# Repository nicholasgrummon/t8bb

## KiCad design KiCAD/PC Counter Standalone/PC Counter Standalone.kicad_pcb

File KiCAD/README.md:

# KiCAD Schematics
I originally designed and assembled t8bb in January 2022 as a hobby project in college (just in my free time, not for credit).<br>
I revisited the project in Fall 2024 after graduating to consider upgrading the computer into a more robust PCB kit that I could potentially sell.
Here I have committed my KiCAD schematics and PCB layouts for the intended upgrade.<br>
However, the upgrade did not come to pass at the time because the supplier I ended up ordering from applied the SMD LEDs backwards.<br>
Not realizing this, I burned out the LEDs on the first board I powered up. I had ordered a handful and tried to desolder and reorient the other LEDs but ruined the boards.
I tried to place several more smaller orders with the same supplier, but they reversed the polarity of the LEDs each time.
So I had to give up on making PCBs for the time.<br>

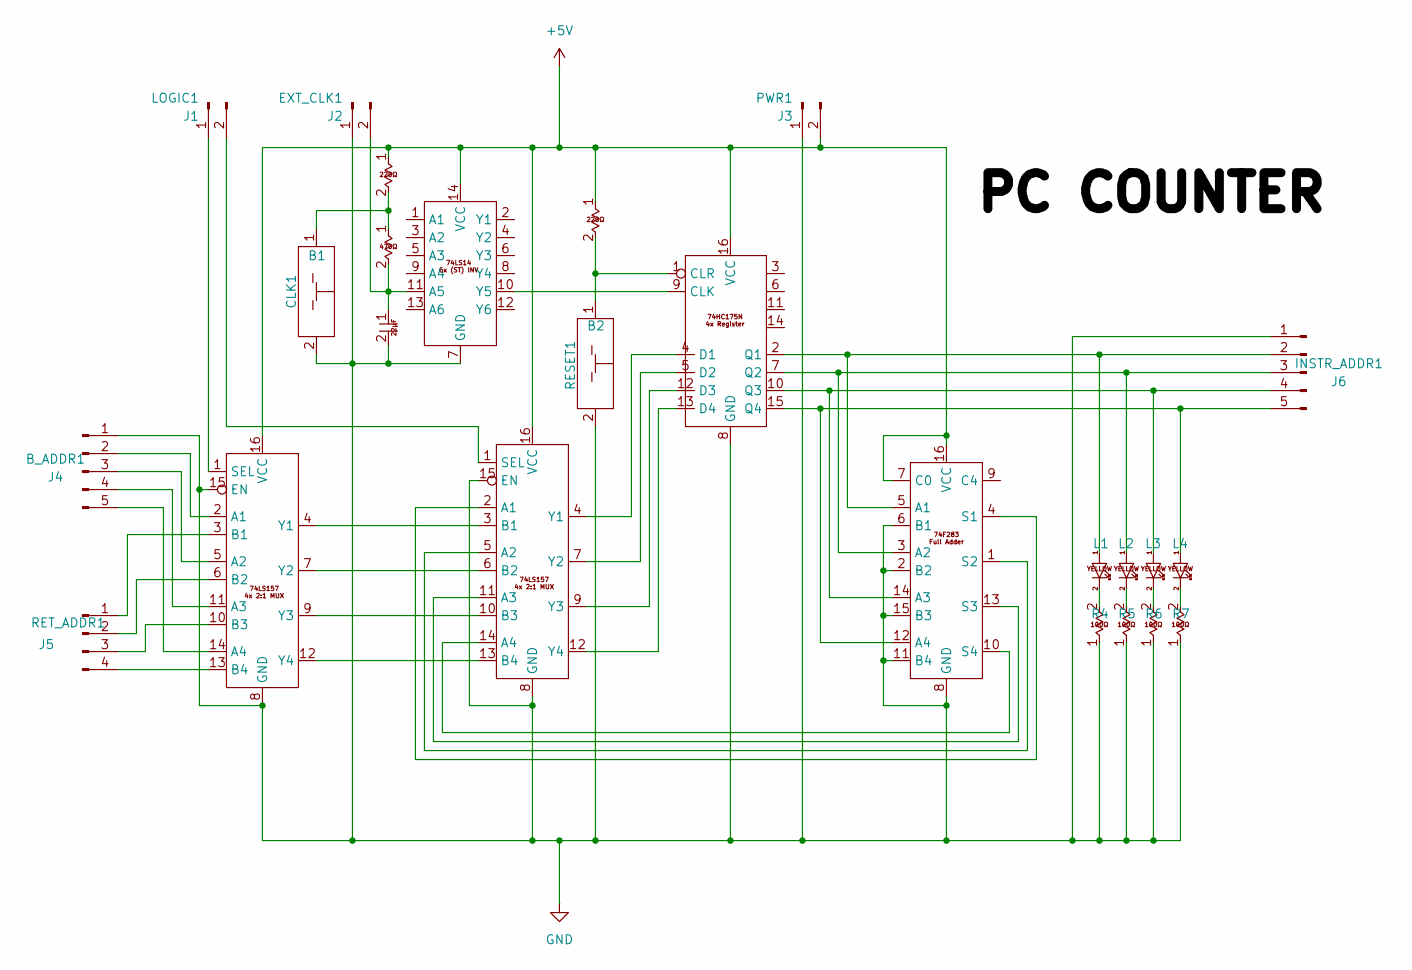
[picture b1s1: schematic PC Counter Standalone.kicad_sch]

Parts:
22μF1: C1; CP_Elec_4x5.4
100Ω1: R4; R_0805_2012Metric
100Ω2: R5; R_0805_2012Metric
100Ω3: R6; R_0805_2012Metric
100Ω4: R7; R_0805_2012Metric
220Ω1: R1; R_0805_2012Metric
220Ω2: R3; R_0805_2012Metric
470Ω1: R2; R_0805_2012Metric
ADD1: U5; 16pinbase
B_ADDR1: J4; PinHeader_1x05_P2.54mm_Vertical
CLK1: B1; SW_Tactile_SPST_NO_Straight_CK_PTS636Sx25SMTRLFS; LCSC C7419906
EXT_CLK1: J2; PinHeader_1x02_P2.54mm_Vertical
INSTR_ADDR1: J6; PinHeader_1x05_P2.54mm_Vertical
LED_YELLOW1: L1; LED_0805_2012Metric; LCSC C2296
LED_YELLOW2: L2; LED_0805_2012Metric; LCSC C2296
LED_YELLOW3: L3; LED_0805_2012Metric; LCSC C2296
LED_YELLOW4: L4; LED_0805_2012Metric; LCSC C2296
LOGIC1: J1; PinHeader_1x02_P2.54mm_Vertical
MUX1: U3; 16pinbase; LCSC C707097
MUX2: U4; 16pinbase
PWR1: J3; PinHeader_1x02_P2.54mm_Vertical
REG1: U2; 16pinbase
RESET1: B2; SW_Tactile_SPST_NO_Straight_CK_PTS636Sx25SMTRLFS; LCSC C7419906
RET_ADDR1: J5; PinHeader_1x04_P2.54mm_Vertical
ST_INV1: U1; 14pinbase; LCSC C609749

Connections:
+5V: 220Ω1.1, 220Ω2.1, ADD1.7 (C0), ADD1.16 (VCC), MUX1.16 (VCC), MUX2.16 (VCC), PWR1.2, REG1.16 (VCC), ST_INV1.14 (VCC)
GND: 22μF1.2, 100Ω1.1, 100Ω2.1, 100Ω3.1, 100Ω4.1, ADD1.2 (B2), ADD1.6 (B1), ADD1.8 (GND), ADD1.11 (B4), ADD1.15 (B3), B_ADDR1.1, CLK1.2, EXT_CLK1.1, INSTR_ADDR1.1, MUX1.8 (GND), MUX1.15 (EN), MUX2.8 (GND), MUX2.15 (EN), PWR1.1, REG1.8 (GND), RESET1.2, ST_INV1.7 (GND)
unnamed: 100Ω1.2, LED_YELLOW1.2
unnamed: 100Ω2.2, LED_YELLOW2.2
unnamed: 100Ω3.2, LED_YELLOW3.2
unnamed: 100Ω4.2, LED_YELLOW4.2
unnamed: 220Ω1.2, 470Ω1.1, CLK1.1
unnamed: ADD1.5 (A1), INSTR_ADDR1.2, LED_YELLOW1.1, REG1.2 (Q1)
unnamed: ADD1.3 (A2), INSTR_ADDR1.3, LED_YELLOW2.1, REG1.7 (Q2)
unnamed: ADD1.14 (A3), INSTR_ADDR1.4, LED_YELLOW3.1, REG1.10 (Q3)
unnamed: ADD1.12 (A4), INSTR_ADDR1.5, LED_YELLOW4.1, REG1.15 (Q4)
unnamed: ADD1.4 (S1), MUX2.2 (A1)
unnamed: ADD1.1 (S2), MUX2.5 (A2)
unnamed: ADD1.13 (S3), MUX2.11 (A3)
unnamed: ADD1.10 (S4), MUX2.14 (A4)
unnamed: B_ADDR1.2, MUX1.2 (A1)
unnamed: B_ADDR1.3, MUX1.5 (A2)
unnamed: B_ADDR1.4, MUX1.11 (A3)
unnamed: B_ADDR1.5, MUX1.14 (A4)
unnamed: 22μF1.1, 470Ω1.2, EXT_CLK1.2, ST_INV1.11 (A5)
unnamed: LOGIC1.1, MUX1.1 (SEL)
unnamed: LOGIC1.2, MUX2.1 (SEL)
unnamed: MUX1.3 (B1), RET_ADDR1.1
unnamed: MUX1.6 (B2), RET_ADDR1.2
unnamed: MUX1.10 (B3), RET_ADDR1.3
unnamed: MUX1.13 (B4), RET_ADDR1.4
unnamed: MUX1.4 (Y1), MUX2.3 (B1)
unnamed: MUX1.7 (Y2), MUX2.6 (B2)
unnamed: MUX1.9 (Y3), MUX2.10 (B3)
unnamed: MUX1.12 (Y4), MUX2.13 (B4)
unnamed: MUX2.4 (Y1), REG1.4 (D1)
unnamed: MUX2.7 (Y2), REG1.5 (D2)
unnamed: MUX2.9 (Y3), REG1.12 (D3)
unnamed: MUX2.12 (Y4), REG1.13 (D4)
unnamed: REG1.9 (CLK), ST_INV1.10 (Y5)
unnamed: 220Ω2.2, REG1.1 (CLR), RESET1.1

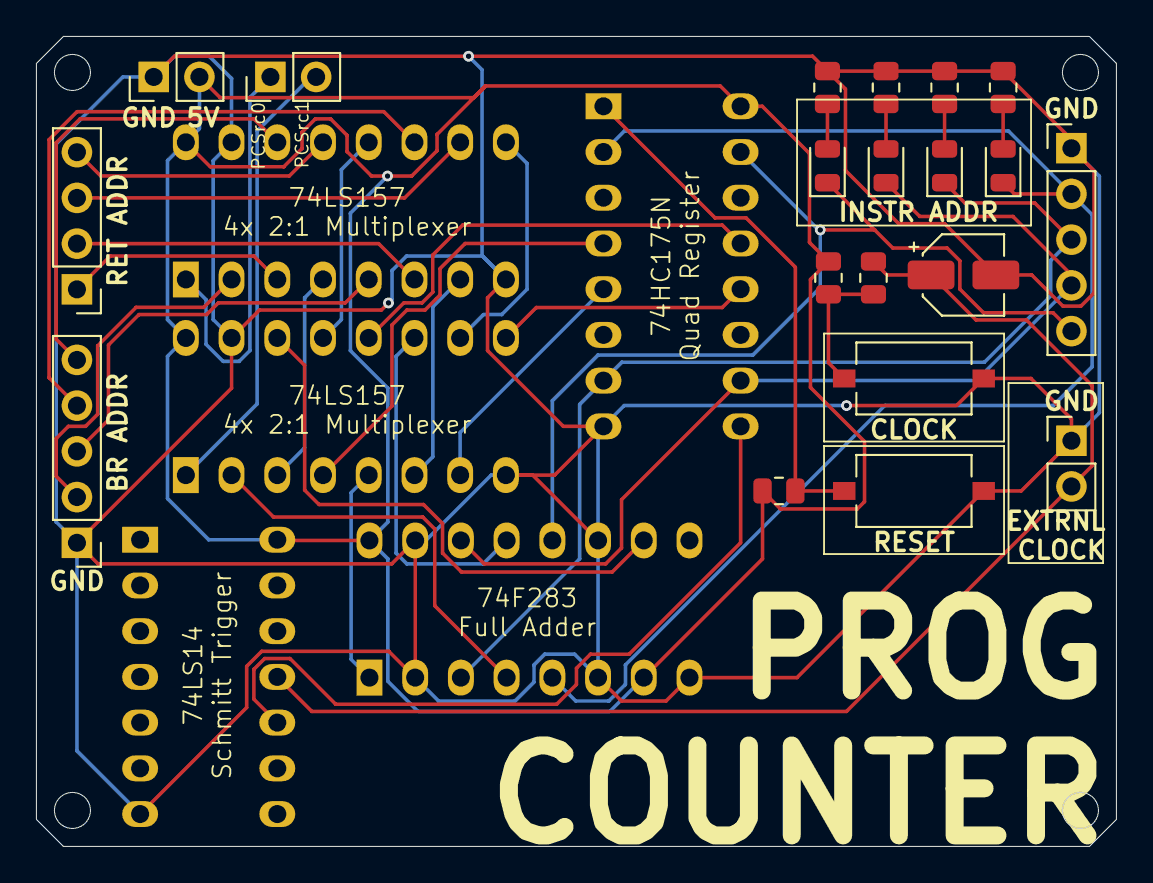
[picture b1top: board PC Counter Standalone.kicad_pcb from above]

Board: 2 copper layers, 60.0 x 45.0 mm, 25 parts (0 on the bottom side), 36 nets.

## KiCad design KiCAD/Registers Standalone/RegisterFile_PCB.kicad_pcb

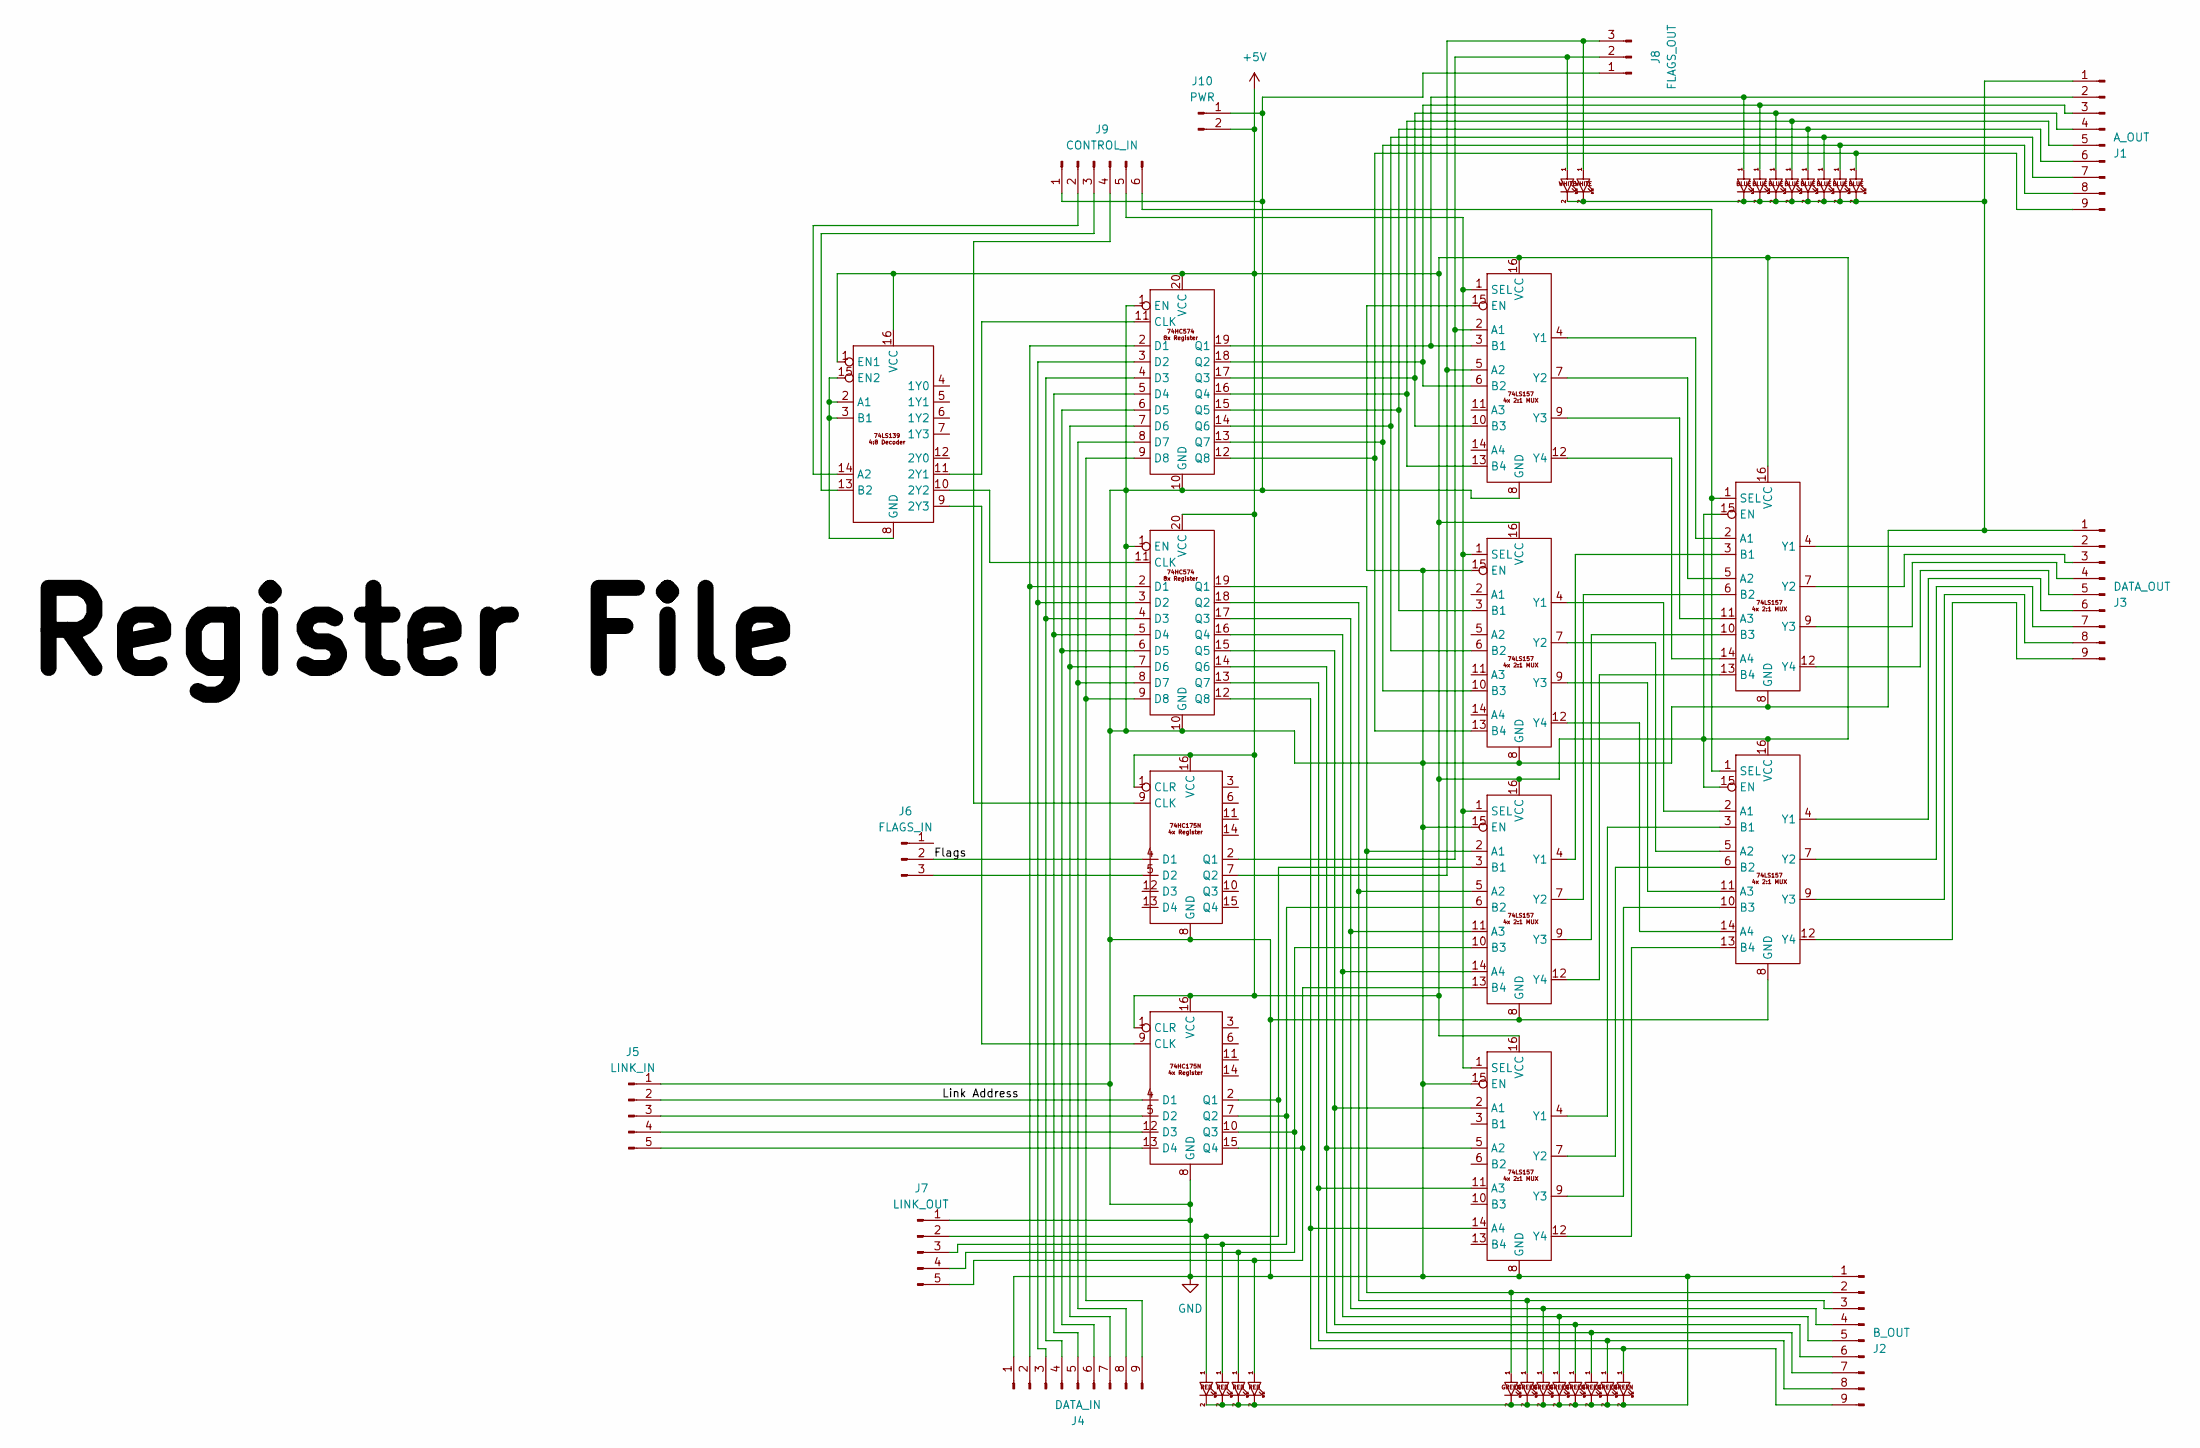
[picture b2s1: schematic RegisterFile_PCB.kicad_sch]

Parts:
74HC1, 74HC2: 20pinbase
74HC175N1, 74HC175N2, 74LS1, 74LS2, 74LS3, 74LS4, 74LS5, 74LS6, 74LS7: 16pinbase
J1: A_OUT; PinHeader_1x09_P2.54mm_Vertical
J2: B_OUT; PinHeader_1x09_P2.54mm_Vertical
J3: DATA_OUT; PinHeader_1x09_P2.54mm_Vertical
J4: DATA_IN; PinHeader_1x09_P2.54mm_Vertical
J5: LINK_IN; PinHeader_1x05_P2.54mm_Vertical
J6: FLAGS_IN; PinHeader_1x03_P2.54mm_Vertical
J7: LINK_OUT; PinHeader_1x05_P2.54mm_Vertical
J8: FLAGS_OUT; PinHeader_1x03_P2.54mm_Vertical
J9: CONTROL_IN; PinHeader_1x06_P2.54mm_Vertical
J10: PWR; PinHeader_1x02_P2.54mm_Vertical
LED_BLUE1, LED_BLUE2, LED_BLUE3, LED_BLUE4, LED_BLUE5, LED_BLUE6, LED_BLUE7, LED_BLUE8: LED_0805_2012Metric
LED_GREEN1, LED_GREEN2, LED_GREEN3, LED_GREEN4, LED_GREEN5, LED_GREEN6, LED_GREEN7, LED_GREEN8: LED_0805_2012Metric
LED_RED1, LED_RED2, LED_RED3, LED_RED4: LED_0805_2012Metric
LED_WHITE1, LED_WHITE2: LED_0805_2012Metric

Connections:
+5V: 74HC1.20 (VCC), 74HC2.20 (VCC), 74HC175N1.1 (CLR), 74HC175N1.16 (VCC), 74HC175N2.1 (CLR), 74HC175N2.16 (VCC), 74LS1.1 (EN1), 74LS1.16 (VCC), 74LS2.16 (VCC), 74LS3.16 (VCC), 74LS4.16 (VCC), 74LS5.16 (VCC), 74LS6.15 (EN), 74LS6.16 (VCC), 74LS7.15 (EN), 74LS7.16 (VCC), J10.2
/Flags: 74HC175N1.4 (D1), J6.2
/Link Address: 74HC175N2.4 (D1), J5.2
GND: 74HC1.1 (EN), 74HC1.10 (GND), 74HC2.1 (EN), 74HC2.10 (GND), 74HC175N1.8 (GND), 74HC175N2.8 (GND), 74LS2.8 (GND), 74LS2.15 (EN), 74LS3.8 (GND), 74LS3.15 (EN), 74LS4.8 (GND), 74LS4.15 (EN), 74LS5.8 (GND), 74LS5.15 (EN), 74LS6.8 (GND), 74LS7.8 (GND), J1.1, J2.1, J3.1, J4.1, J5.1, J7.1, J8.1, J9.1, J10.1, LED_BLUE1.2, LED_BLUE2.2, LED_BLUE3.2, LED_BLUE4.2, LED_BLUE5.2, LED_BLUE6.2, LED_BLUE7.2, LED_BLUE8.2, LED_GREEN1.2, LED_GREEN2.2, LED_GREEN3.2, LED_GREEN4.2, LED_GREEN5.2, LED_GREEN6.2, LED_GREEN7.2, LED_GREEN8.2, LED_RED1.2, LED_RED2.2, LED_RED3.2, LED_RED4.2, LED_WHITE1.2, LED_WHITE2.2
unnamed: 74HC1.11 (CLK), 74LS1.11 (2Y1)
unnamed: 74HC1.2 (D1), 74HC2.2 (D1), J4.2
unnamed: 74HC1.3 (D2), 74HC2.3 (D2), J4.3
unnamed: 74HC1.4 (D3), 74HC2.4 (D3), J4.4
unnamed: 74HC1.5 (D4), 74HC2.5 (D4), J4.5
unnamed: 74HC1.6 (D5), 74HC2.6 (D5), J4.6
unnamed: 74HC1.7 (D6), 74HC2.7 (D6), J4.7
unnamed: 74HC1.8 (D7), 74HC2.8 (D7), J4.8
unnamed: 74HC1.9 (D8), 74HC2.9 (D8), J4.9
unnamed: 74HC1.19 (Q1), 74LS2.3 (B1), J1.2, LED_BLUE1.1
unnamed: 74HC1.18 (Q2), 74LS2.6 (B2), J1.3, LED_BLUE2.1
unnamed: 74HC1.17 (Q3), 74LS2.10 (B3), J1.4, LED_BLUE3.1
unnamed: 74HC1.16 (Q4), 74LS2.13 (B4), J1.5, LED_BLUE4.1
unnamed: 74HC1.15 (Q5), 74LS3.3 (B1), J1.6, LED_BLUE5.1
unnamed: 74HC1.14 (Q6), 74LS3.6 (B2), J1.7, LED_BLUE6.1
unnamed: 74HC1.13 (Q7), 74LS3.10 (B3), J1.8, LED_BLUE7.1
unnamed: 74HC1.12 (Q8), 74LS3.13 (B4), J1.9, LED_BLUE8.1
unnamed: 74HC2.11 (CLK), 74LS1.10 (2Y2)
unnamed: 74HC2.19 (Q1), 74LS4.2 (A1), J2.2, LED_GREEN1.1
unnamed: 74HC2.18 (Q2), 74LS4.5 (A2), J2.3, LED_GREEN2.1
unnamed: 74HC2.17 (Q3), 74LS4.11 (A3), J2.4, LED_GREEN3.1
unnamed: 74HC2.16 (Q4), 74LS4.14 (A4), J2.5, LED_GREEN4.1
unnamed: 74HC2.15 (Q5), 74LS5.2 (A1), J2.6, LED_GREEN5.1
unnamed: 74HC2.14 (Q6), 74LS5.5 (A2), J2.7, LED_GREEN6.1
unnamed: 74HC2.13 (Q7), 74LS5.11 (A3), J2.8, LED_GREEN7.1
unnamed: 74HC2.12 (Q8), 74LS5.14 (A4), J2.9, LED_GREEN8.1
unnamed: 74HC175N1.9 (CLK), J9.4
unnamed: 74HC175N1.5 (D2), J6.3
unnamed: 74HC175N1.2 (Q1), 74LS2.2 (A1), J8.2, LED_WHITE1.1
unnamed: 74HC175N1.7 (Q2), 74LS2.5 (A2), J8.3, LED_WHITE2.1
unnamed: 74HC175N2.9 (CLK), 74LS1.9 (2Y3)
unnamed: 74HC175N2.5 (D2), J5.3
unnamed: 74HC175N2.12 (D3), J5.4
unnamed: 74HC175N2.13 (D4), J5.5
unnamed: 74HC175N2.2 (Q1), 74LS4.3 (B1), J7.2, LED_RED1.1
unnamed: 74HC175N2.7 (Q2), 74LS4.6 (B2), J7.3, LED_RED2.1
unnamed: 74HC175N2.10 (Q3), 74LS4.10 (B3), J7.4, LED_RED3.1
unnamed: 74HC175N2.15 (Q4), 74LS4.13 (B4), J7.5, LED_RED4.1
unnamed: 74LS1.2 (A1), 74LS1.3 (B1), 74LS1.8 (GND), 74LS1.15 (EN2)
unnamed: 74LS1.14 (A2), J9.2
unnamed: 74LS1.13 (B2), J9.3
unnamed: 74LS2.1 (SEL), 74LS3.1 (SEL), 74LS4.1 (SEL), 74LS5.1 (SEL), J9.5
unnamed: 74LS2.4 (Y1), 74LS6.2 (A1)
unnamed: 74LS2.7 (Y2), 74LS6.5 (A2)
unnamed: 74LS2.9 (Y3), 74LS6.11 (A3)
unnamed: 74LS2.12 (Y4), 74LS6.14 (A4)
unnamed: 74LS3.4 (Y1), 74LS7.2 (A1)
unnamed: 74LS3.7 (Y2), 74LS7.5 (A2)
unnamed: 74LS3.9 (Y3), 74LS7.11 (A3)
unnamed: 74LS3.12 (Y4), 74LS7.14 (A4)
unnamed: 74LS4.4 (Y1), 74LS6.3 (B1)
unnamed: 74LS4.7 (Y2), 74LS6.6 (B2)
unnamed: 74LS4.9 (Y3), 74LS6.10 (B3)
unnamed: 74LS4.12 (Y4), 74LS6.13 (B4)
unnamed: 74LS5.4 (Y1), 74LS7.3 (B1)
unnamed: 74LS5.7 (Y2), 74LS7.6 (B2)
unnamed: 74LS5.9 (Y3), 74LS7.10 (B3)
unnamed: 74LS5.12 (Y4), 74LS7.13 (B4)
unnamed: 74LS6.1 (SEL), 74LS7.1 (SEL), J9.6
unnamed: 74LS6.4 (Y1), J3.2
unnamed: 74LS6.7 (Y2), J3.3
unnamed: 74LS6.9 (Y3), J3.4
unnamed: 74LS6.12 (Y4), J3.5
unnamed: 74LS7.4 (Y1), J3.6
unnamed: 74LS7.7 (Y2), J3.7
unnamed: 74LS7.9 (Y3), J3.8
unnamed: 74LS7.12 (Y4), J3.9

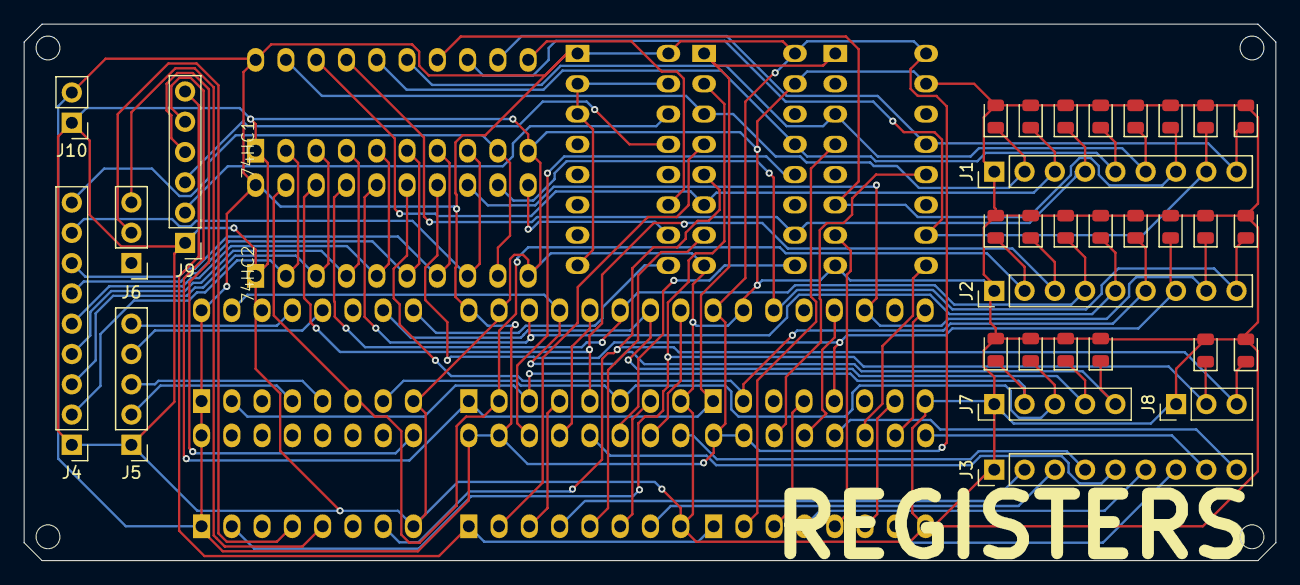
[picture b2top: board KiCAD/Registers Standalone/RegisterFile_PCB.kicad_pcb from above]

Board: 2 copper layers, 105.0 x 45.0 mm, 43 parts (0 on the bottom side), 71 nets.

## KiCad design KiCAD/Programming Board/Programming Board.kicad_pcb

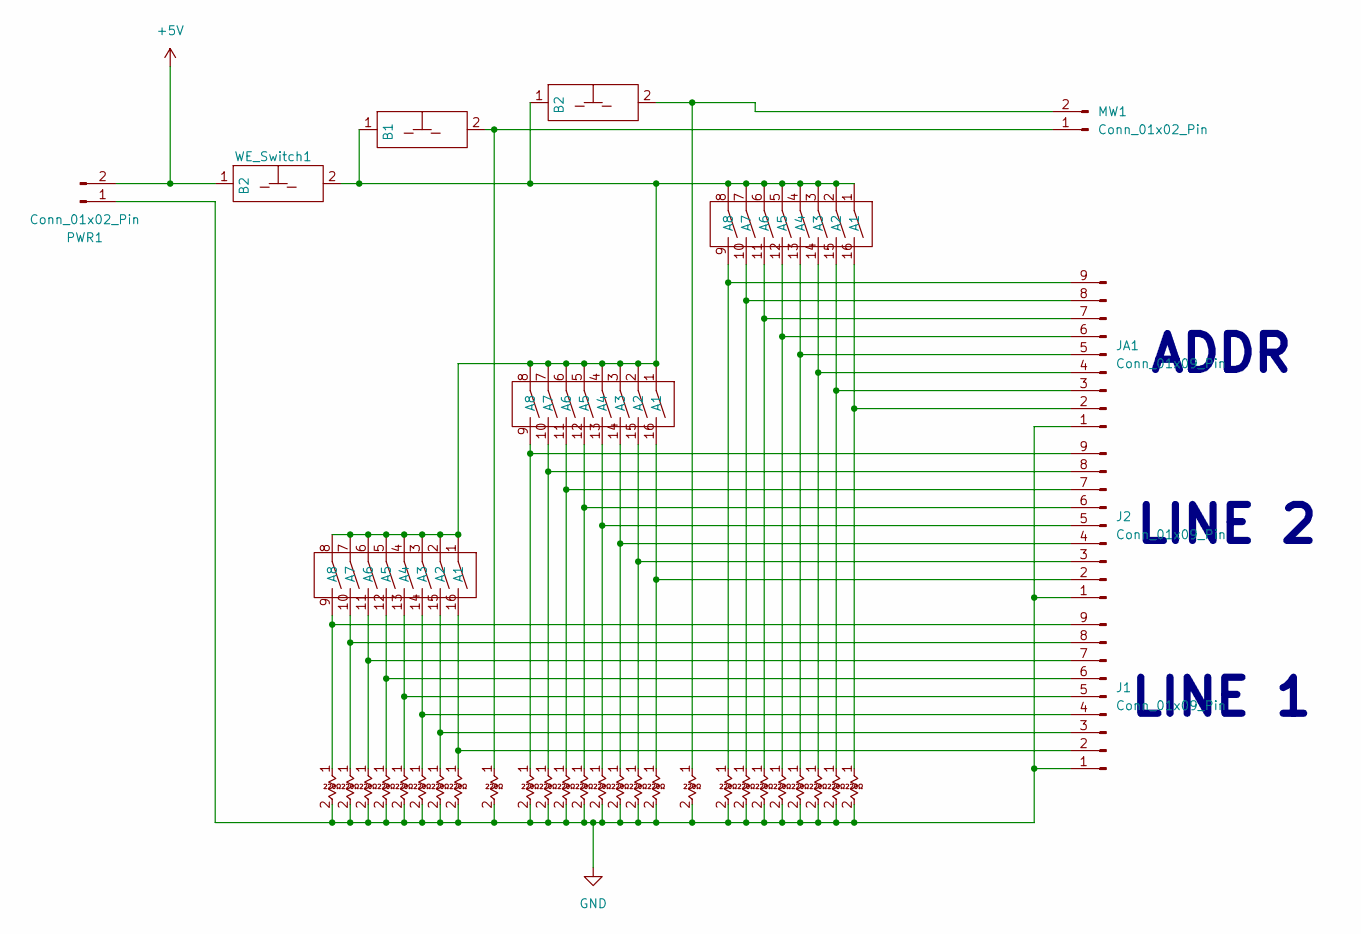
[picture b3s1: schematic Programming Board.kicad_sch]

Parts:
2xPushButtonB1: B1; SW_Tactile_SPST_NO_Straight_CK_PTS636Sx25SMTRLFS; LCSC C7419906
2xPushButtonB2: B2; SW_Tactile_SPST_NO_Straight_CK_PTS636Sx25SMTRLFS; LCSC C7419906
8xDIP1, 8xDIP2, 8xDIPA1: 16pinbase
220Ω11111, 220Ω12111, 220Ω13111, 220Ω14111, 220Ω15111, 220Ω16111, 220Ω17111, 220Ω18111, 220Ω21111, 220Ω22111, 220Ω23111, 220Ω24111, 220Ω25111, 220Ω26111, 220Ω27111, 220Ω28111, 220ΩA1, 220ΩA2, 220ΩA3, 220ΩA4, 220ΩB1, 220ΩB2, 220ΩB3, 220ΩB4: R_0402_1005Metric
220ΩP1, 220ΩP2: R_1210_3225Metric
J1, J2: Conn_01x09_Pin; PinHeader_1x09_P2.54mm_Vertical
JA1: Conn_01x09_Pin; PinHeader_1x09_P2.54mm_Vertical
MW1: Conn_01x02_Pin; PinHeader_1x02_P2.54mm_Vertical
PWR1: Conn_01x02_Pin; PinHeader_1x02_P2.54mm_Vertical
WE_Switch1: B2; SW_Tactile_SPST_NO_Straight_CK_PTS636Sx25SMTRLFS; LCSC C7419906

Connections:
+5V: PWR1.2, WE_Switch1.1
GND: 220Ω11111.2, 220Ω12111.2, 220Ω13111.2, 220Ω14111.2, 220Ω15111.2, 220Ω16111.2, 220Ω17111.2, 220Ω18111.2, 220Ω21111.2, 220Ω22111.2, 220Ω23111.2, 220Ω24111.2, 220Ω25111.2, 220Ω26111.2, 220Ω27111.2, 220Ω28111.2, 220ΩA1.2, 220ΩA2.2, 220ΩA3.2, 220ΩA4.2, 220ΩB1.2, 220ΩB2.2, 220ΩB3.2, 220ΩB4.2, 220ΩP1.2, 220ΩP2.2, J1.1, J2.1, JA1.1, PWR1.1
unnamed: 2xPushButtonB1.1, 2xPushButtonB2.1, 8xDIP1.1 (A1), 8xDIP1.2 (A2), 8xDIP1.3 (A3), 8xDIP1.4 (A4), 8xDIP1.5 (A5), 8xDIP1.6 (A6), 8xDIP1.7 (A7), 8xDIP1.8 (A8), 8xDIP2.1 (A1), 8xDIP2.2 (A2), 8xDIP2.3 (A3), 8xDIP2.4 (A4), 8xDIP2.5 (A5), 8xDIP2.6 (A6), 8xDIP2.7 (A7), 8xDIP2.8 (A8), 8xDIPA1.1 (A1), 8xDIPA1.2 (A2), 8xDIPA1.3 (A3), 8xDIPA1.4 (A4), 8xDIPA1.5 (A5), 8xDIPA1.6 (A6), 8xDIPA1.7 (A7), 8xDIPA1.8 (A8), WE_Switch1.2
unnamed: 8xDIP1.16, 220Ω11111.1, J1.2
unnamed: 8xDIP1.15, 220Ω12111.1, J1.3
unnamed: 8xDIP1.14, 220Ω13111.1, J1.4
unnamed: 8xDIP1.13, 220Ω14111.1, J1.5
unnamed: 8xDIP1.12, 220Ω15111.1, J1.6
unnamed: 8xDIP1.11, 220Ω16111.1, J1.7
unnamed: 8xDIP1.10, 220Ω17111.1, J1.8
unnamed: 8xDIP1.9, 220Ω18111.1, J1.9
unnamed: 8xDIP2.16, 220Ω21111.1, J2.2
unnamed: 8xDIP2.15, 220Ω22111.1, J2.3
unnamed: 8xDIP2.14, 220Ω23111.1, J2.4
unnamed: 8xDIP2.13, 220Ω24111.1, J2.5
unnamed: 8xDIP2.12, 220Ω25111.1, J2.6
unnamed: 8xDIP2.11, 220Ω26111.1, J2.7
unnamed: 8xDIP2.10, 220Ω27111.1, J2.8
unnamed: 8xDIP2.9, 220Ω28111.1, J2.9
unnamed: 8xDIPA1.16, 220ΩA1.1, JA1.2
unnamed: 8xDIPA1.15, 220ΩA2.1, JA1.3
unnamed: 8xDIPA1.14, 220ΩA3.1, JA1.4
unnamed: 8xDIPA1.13, 220ΩA4.1, JA1.5
unnamed: 8xDIPA1.12, 220ΩB1.1, JA1.6
unnamed: 8xDIPA1.11, 220ΩB2.1, JA1.7
unnamed: 8xDIPA1.10, 220ΩB3.1, JA1.8
unnamed: 8xDIPA1.9, 220ΩB4.1, JA1.9
unnamed: 2xPushButtonB1.2, 220ΩP1.1, MW1.1
unnamed: 2xPushButtonB2.2, 220ΩP2.1, MW1.2

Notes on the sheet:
ADDR
LINE 2
LINE 1

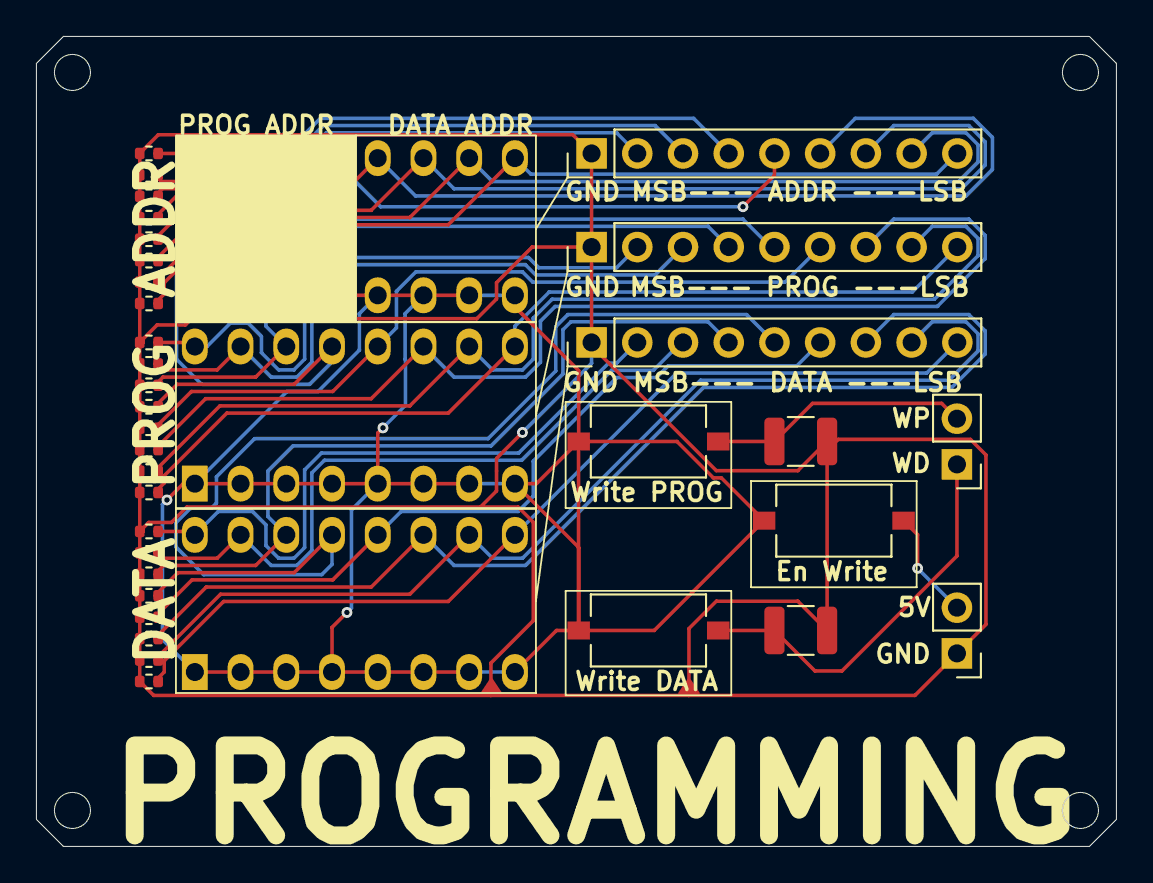
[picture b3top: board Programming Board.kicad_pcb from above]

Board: 2 copper layers, 60.0 x 45.0 mm, 37 parts (0 on the bottom side), 29 nets.

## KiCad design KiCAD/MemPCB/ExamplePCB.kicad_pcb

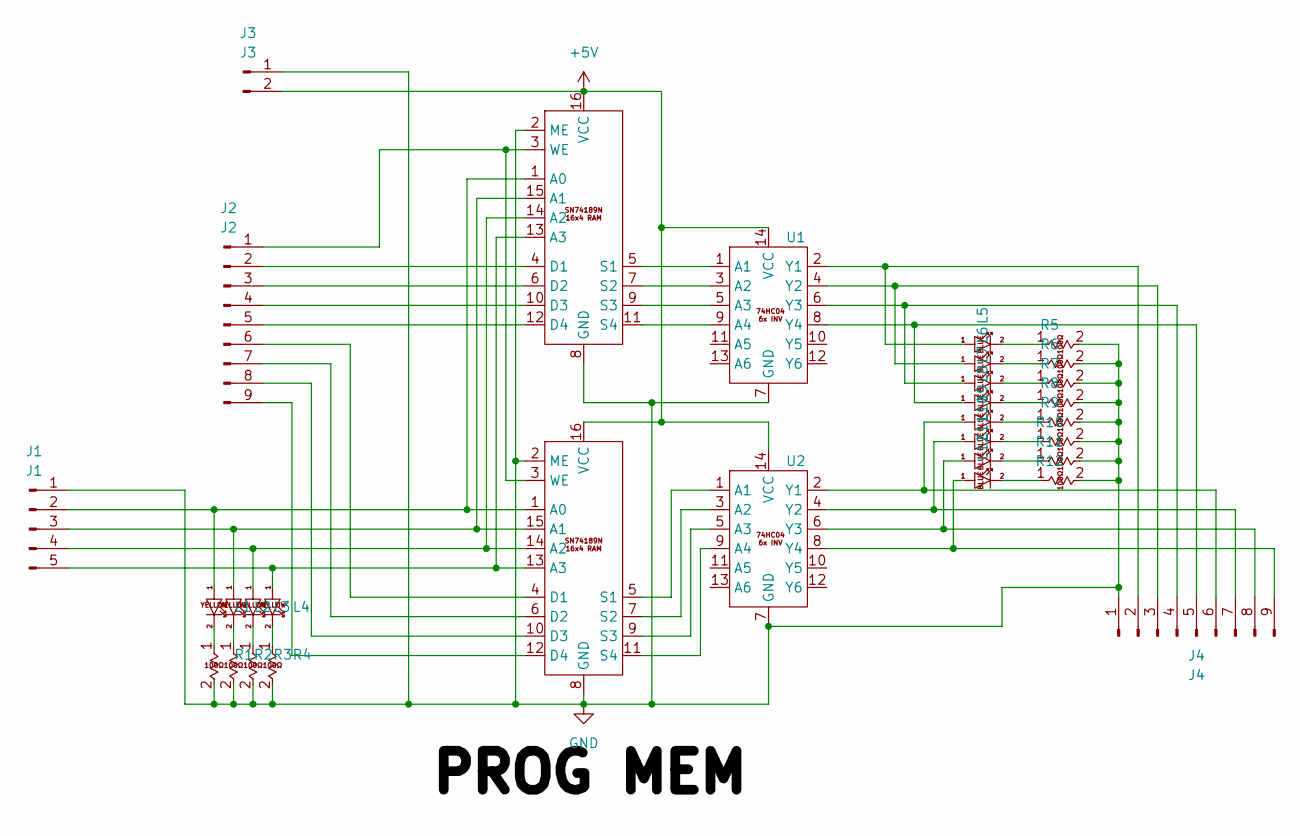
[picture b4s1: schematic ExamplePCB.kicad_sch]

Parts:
74HC1: U1; 14pinbase; LCSC C18723497
74HC2: U2; 14pinbase; LCSC C18723497
100Ω11: R1; R_0805_2012Metric; LCSC C2907294
100Ω12: R5; R_0805_2012Metric; LCSC C2907294
100Ω111: R2; R_0805_2012Metric; LCSC C2907294
100Ω112: R3; R_0805_2012Metric; LCSC C2907294
100Ω113: R4; R_0805_2012Metric; LCSC C2907294
100Ω114: R6; R_0805_2012Metric; LCSC C2907294
100Ω1111: R7; R_0805_2012Metric; LCSC C2907294
100Ω1112: R8; R_0805_2012Metric; LCSC C2907294
100Ω1113: R9; R_0805_2012Metric; LCSC C2907294
100Ω1114: R10; R_0805_2012Metric; LCSC C2907294
100Ω1115: R11; R_0805_2012Metric; LCSC C2907294
100Ω1116: R12; R_0805_2012Metric; LCSC C2907294
J1: J1; PinHeader_1x05_P2.54mm_Vertical; LCSC C6332198
J2: J2; PinHeader_1x09_P2.54mm_Vertical; LCSC C27985193
J3: J3; PinHeader_1x02_P2.54mm_Vertical; LCSC C492401
J4: J4; PinHeader_1x09_P2.54mm_Vertical; LCSC C27985193
LED_BLUE1: L5; LED_0805_2012Metric; LCSC C7371912
LED_BLUE2: L6; LED_0805_2012Metric; LCSC C7371912
LED_BLUE3: L7; LED_0805_2012Metric; LCSC C7371912
LED_BLUE4: L8; LED_0805_2012Metric; LCSC C7371912
LED_BLUE5: L9; LED_0805_2012Metric; LCSC C7371912
LED_BLUE6: L10; LED_0805_2012Metric; LCSC C7371912
LED_BLUE7: L11; LED_0805_2012Metric; LCSC C7371912
LED_BLUE8: L12; LED_0805_2012Metric; LCSC C7371912
LED_YELLOW1: L1; LED_0805_2012Metric; LCSC C2296
LED_YELLOW2: L2; LED_0805_2012Metric; LCSC C2296
LED_YELLOW3: L3; LED_0805_2012Metric; LCSC C2296
LED_YELLOW4: L4; LED_0805_2012Metric; LCSC C2296
SN74189N1, SN74189N2: 16pinbase

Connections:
+5V: 74HC1.14 (VCC), 74HC2.14 (VCC), J3.2, SN74189N1.16 (VCC), SN74189N2.16 (VCC)
GND: 74HC1.7 (GND), 74HC2.7 (GND), 100Ω11.2, 100Ω12.2, 100Ω111.2, 100Ω112.2, 100Ω113.2, 100Ω114.2, 100Ω1111.2, 100Ω1112.2, 100Ω1113.2, 100Ω1114.2, 100Ω1115.2, 100Ω1116.2, J1.1, J3.1, J4.1, SN74189N1.2 (ME), SN74189N1.8 (GND), SN74189N2.2 (ME), SN74189N2.8 (GND)
unnamed: 74HC1.1 (A1), SN74189N1.5 (S1)
unnamed: 74HC1.3 (A2), SN74189N1.7 (S2)
unnamed: 74HC1.5 (A3), SN74189N1.9 (S3)
unnamed: 74HC1.9 (A4), SN74189N1.11 (S4)
unnamed: 74HC1.2 (Y1), J4.2, LED_BLUE1.1
unnamed: 74HC1.4 (Y2), J4.3, LED_BLUE2.1
unnamed: 74HC1.6 (Y3), J4.4, LED_BLUE3.1
unnamed: 74HC1.8 (Y4), J4.5, LED_BLUE4.1
unnamed: 74HC2.1 (A1), SN74189N2.5 (S1)
unnamed: 74HC2.3 (A2), SN74189N2.7 (S2)
unnamed: 74HC2.5 (A3), SN74189N2.9 (S3)
unnamed: 74HC2.9 (A4), SN74189N2.11 (S4)
unnamed: 74HC2.2 (Y1), J4.6, LED_BLUE5.1
unnamed: 74HC2.4 (Y2), J4.7, LED_BLUE6.1
unnamed: 74HC2.6 (Y3), J4.8, LED_BLUE7.1
unnamed: 74HC2.8 (Y4), J4.9, LED_BLUE8.1
unnamed: 100Ω11.1, LED_YELLOW1.2
unnamed: 100Ω12.1, LED_BLUE1.2
unnamed: 100Ω111.1, LED_YELLOW2.2
unnamed: 100Ω112.1, LED_YELLOW3.2
unnamed: 100Ω113.1, LED_YELLOW4.2
unnamed: 100Ω114.1, LED_BLUE2.2
unnamed: 100Ω1111.1, LED_BLUE3.2
unnamed: 100Ω1112.1, LED_BLUE4.2
unnamed: 100Ω1113.1, LED_BLUE5.2
unnamed: 100Ω1114.1, LED_BLUE6.2
unnamed: 100Ω1115.1, LED_BLUE7.2
unnamed: 100Ω1116.1, LED_BLUE8.2
unnamed: J1.2, LED_YELLOW1.1, SN74189N1.1 (A0), SN74189N2.1 (A0)
unnamed: J1.3, LED_YELLOW2.1, SN74189N1.15 (A1), SN74189N2.15 (A1)
unnamed: J1.4, LED_YELLOW3.1, SN74189N1.14 (A2), SN74189N2.14 (A2)
unnamed: J1.5, LED_YELLOW4.1, SN74189N1.13 (A3), SN74189N2.13 (A3)
unnamed: J2.1, SN74189N1.3 (WE), SN74189N2.3 (WE)
unnamed: J2.2, SN74189N1.4 (D1)
unnamed: J2.3, SN74189N1.6 (D2)
unnamed: J2.4, SN74189N1.10 (D3)
unnamed: J2.5, SN74189N1.12 (D4)
unnamed: J2.6, SN74189N2.4 (D1)
unnamed: J2.7, SN74189N2.6 (D2)
unnamed: J2.8, SN74189N2.10 (D3)
unnamed: J2.9, SN74189N2.12 (D4)

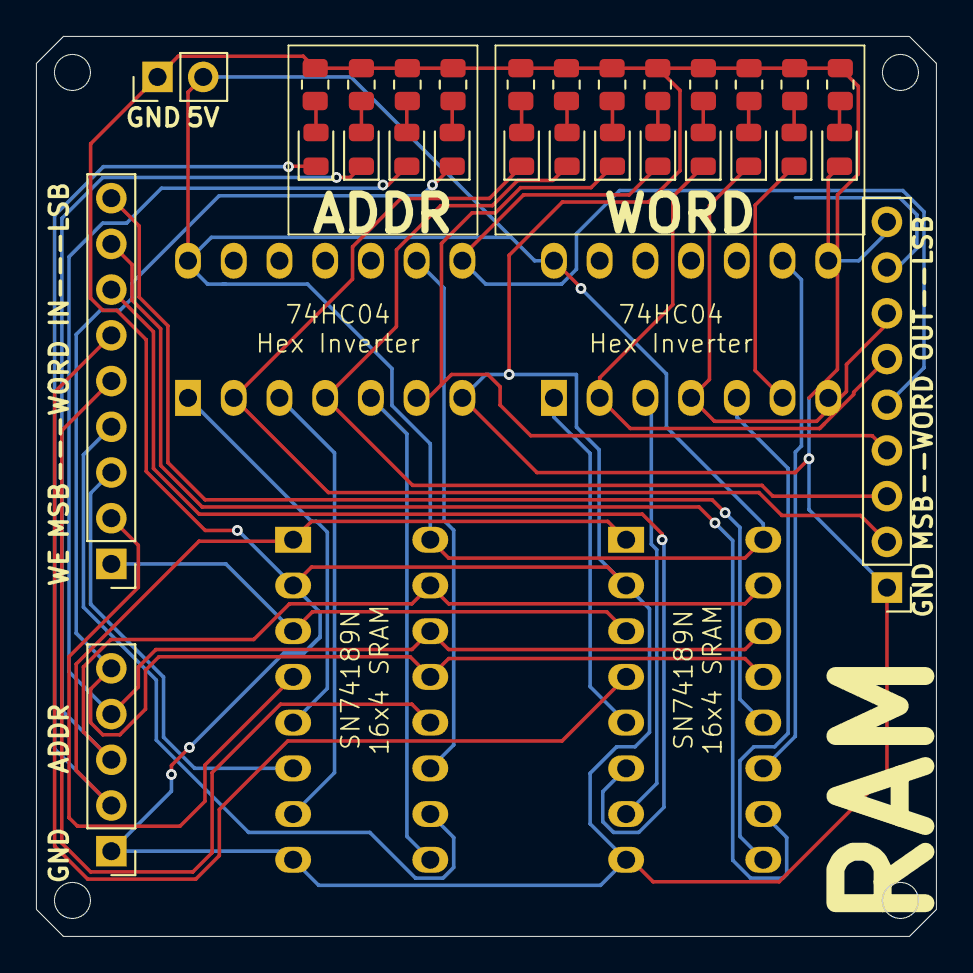
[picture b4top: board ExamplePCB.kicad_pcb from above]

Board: 2 copper layers, 50.0 x 50.0 mm, 32 parts (0 on the bottom side), 43 nets.

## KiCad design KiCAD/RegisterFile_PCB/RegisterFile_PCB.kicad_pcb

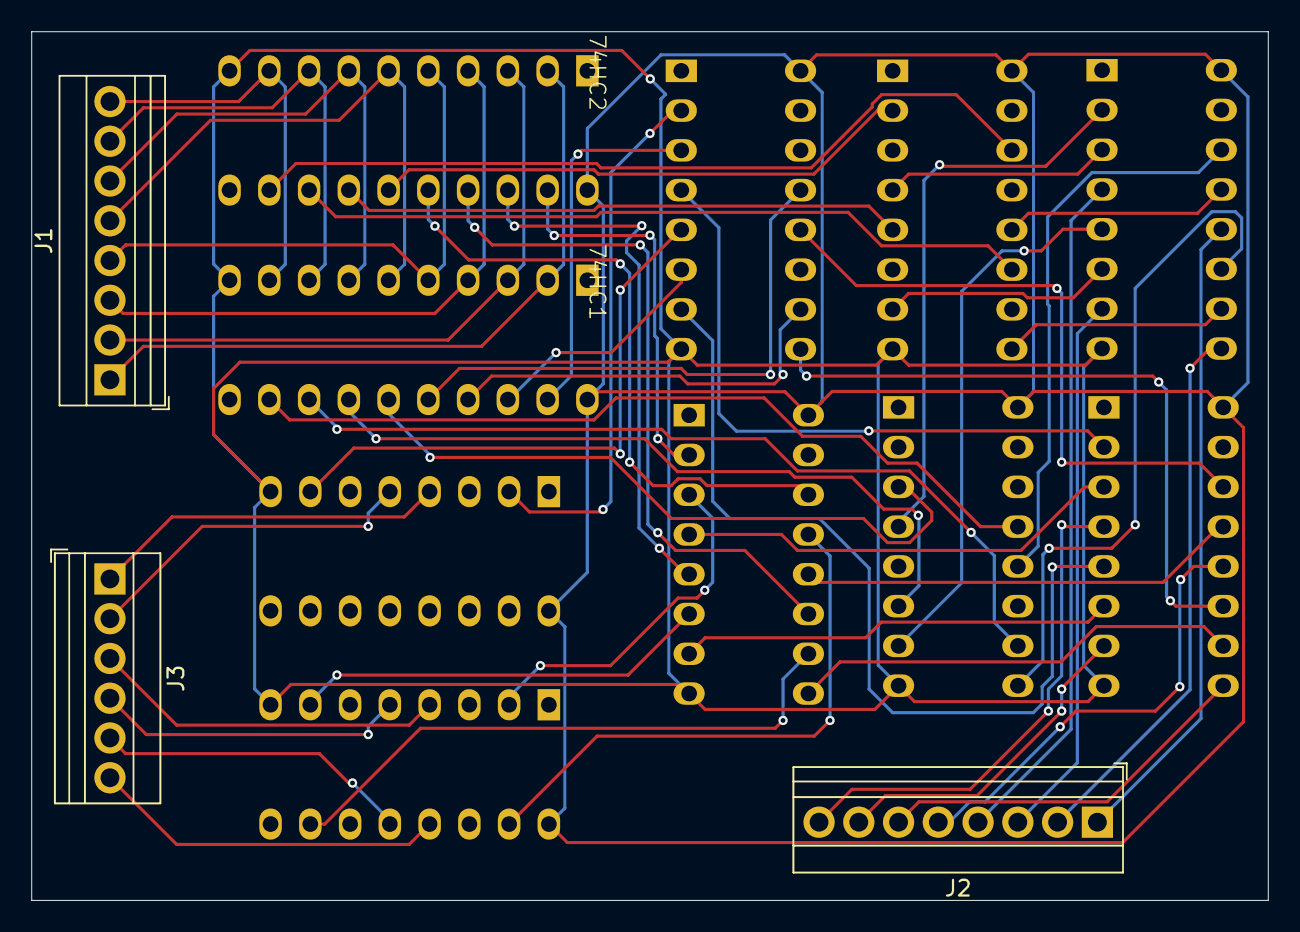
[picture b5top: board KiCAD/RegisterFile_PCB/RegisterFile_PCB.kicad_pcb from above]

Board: 2 copper layers, 79.0 x 55.5 mm, 13 parts (0 on the bottom side), 62 nets.

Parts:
74HC1, 74HC2: 20pinbase
74HC175N1, 74HC175N2, 74LS1, 74LS2, 74LS3, 74LS4, 74LS5, 74LS6: 16pinbase
J1, J2: Conn_01x08_Pin; TerminalBlock_Xinya_XY308-2.54-8P_1x08_P2.54mm_Horizontal
J3: Conn_01x06_Pin; TerminalBlock_Xinya_XY308-2.54-6P_1x06_P2.54mm_Horizontal

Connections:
+5V: 74HC1.20 (VCC), 74HC2.20 (VCC), 74HC175N1.16 (VCC), 74HC175N2.16 (VCC), 74LS1.16 (VCC), 74LS2.16 (VCC), 74LS3.16 (VCC), 74LS4.16 (VCC), 74LS5.16 (VCC), 74LS6.16 (VCC)
/Link Address: 74HC175N2.4 (D1), J3.3
GND: 74HC1.10 (GND), 74HC2.10 (GND), 74HC175N1.8 (GND), 74HC175N2.8 (GND), 74LS1.8 (GND), 74LS2.8 (GND), 74LS3.8 (GND), 74LS4.8 (GND), 74LS5.8 (GND), 74LS6.8 (GND)
unnamed: 74HC1.2 (D1), 74HC2.2 (D1), J1.1
unnamed: 74HC1.3 (D2), 74HC2.3 (D2), J1.2
unnamed: 74HC1.4 (D3), 74HC2.4 (D3), J1.3
unnamed: 74HC1.5 (D4), 74HC2.5 (D4), J1.4
unnamed: 74HC1.6 (D5), 74HC2.6 (D5), J1.5
unnamed: 74HC1.7 (D6), 74HC2.7 (D6), J1.6
unnamed: 74HC1.8 (D7), 74HC2.8 (D7), J1.7
unnamed: 74HC1.9 (D8), 74HC2.9 (D8), J1.8
unnamed: 74HC1.19 (Q1), 74LS1.3 (B1)
unnamed: 74HC1.18 (Q2), 74LS1.6 (B2)
unnamed: 74HC1.17 (Q3), 74LS1.10 (B3)
unnamed: 74HC1.16 (Q4), 74LS1.13 (B4)
unnamed: 74HC1.15 (Q5), 74LS2.3 (B1)
unnamed: 74HC1.14 (Q6), 74LS2.6 (B2)
unnamed: 74HC1.13 (Q7), 74LS2.10 (B3)
unnamed: 74HC1.12 (Q8), 74LS2.13 (B4)
unnamed: 74HC2.19 (Q1), 74LS3.2 (A1)
unnamed: 74HC2.18 (Q2), 74LS3.5 (A2)
unnamed: 74HC2.17 (Q3), 74LS3.11 (A3)
unnamed: 74HC2.16 (Q4), 74LS3.14 (A4)
unnamed: 74HC2.15 (Q5), 74LS4.2 (A1)
unnamed: 74HC2.14 (Q6), 74LS4.5 (A2)
unnamed: 74HC2.13 (Q7), 74LS4.11 (A3)
unnamed: 74HC2.12 (Q8), 74LS4.14 (A4)
unnamed: 74HC175N1.4 (D1), J3.1
unnamed: 74HC175N1.5 (D2), J3.2
unnamed: 74HC175N1.2 (Q1), 74LS1.2 (A1)
unnamed: 74HC175N1.7 (Q2), 74LS1.5 (A2)
unnamed: 74HC175N2.5 (D2), J3.4
unnamed: 74HC175N2.12 (D3), J3.5
unnamed: 74HC175N2.13 (D4), J3.6
unnamed: 74HC175N2.2 (Q1), 74LS3.3 (B1)
unnamed: 74HC175N2.7 (Q2), 74LS3.6 (B2)
unnamed: 74HC175N2.10 (Q3), 74LS3.10 (B3)
unnamed: 74HC175N2.15 (Q4), 74LS3.13 (B4)
unnamed: 74LS1.4 (Y1), 74LS5.2 (A1)
unnamed: 74LS1.7 (Y2), 74LS5.5 (A2)
unnamed: 74LS1.9 (Y3), 74LS5.11 (A3)
unnamed: 74LS1.12 (Y4), 74LS5.14 (A4)
unnamed: 74LS2.4 (Y1), 74LS6.2 (A1)
unnamed: 74LS2.7 (Y2), 74LS6.5 (A2)
unnamed: 74LS2.9 (Y3), 74LS6.11 (A3)
unnamed: 74LS2.12 (Y4), 74LS6.14 (A4)
unnamed: 74LS3.4 (Y1), 74LS5.3 (B1)
unnamed: 74LS3.7 (Y2), 74LS5.6 (B2)
unnamed: 74LS3.9 (Y3), 74LS5.10 (B3)
unnamed: 74LS3.12 (Y4), 74LS5.13 (B4)
unnamed: 74LS4.4 (Y1), 74LS6.3 (B1)
unnamed: 74LS4.7 (Y2), 74LS6.6 (B2)
unnamed: 74LS4.9 (Y3), 74LS6.10 (B3)
unnamed: 74LS4.12 (Y4), 74LS6.13 (B4)
unnamed: 74LS5.4 (Y1), J2.8
unnamed: 74LS5.7 (Y2), J2.7
unnamed: 74LS5.9 (Y3), J2.6
unnamed: 74LS5.12 (Y4), J2.5
unnamed: 74LS6.4 (Y1), J2.4
unnamed: 74LS6.7 (Y2), J2.3
unnamed: 74LS6.9 (Y3), J2.2
unnamed: 74LS6.12 (Y4), J2.1
